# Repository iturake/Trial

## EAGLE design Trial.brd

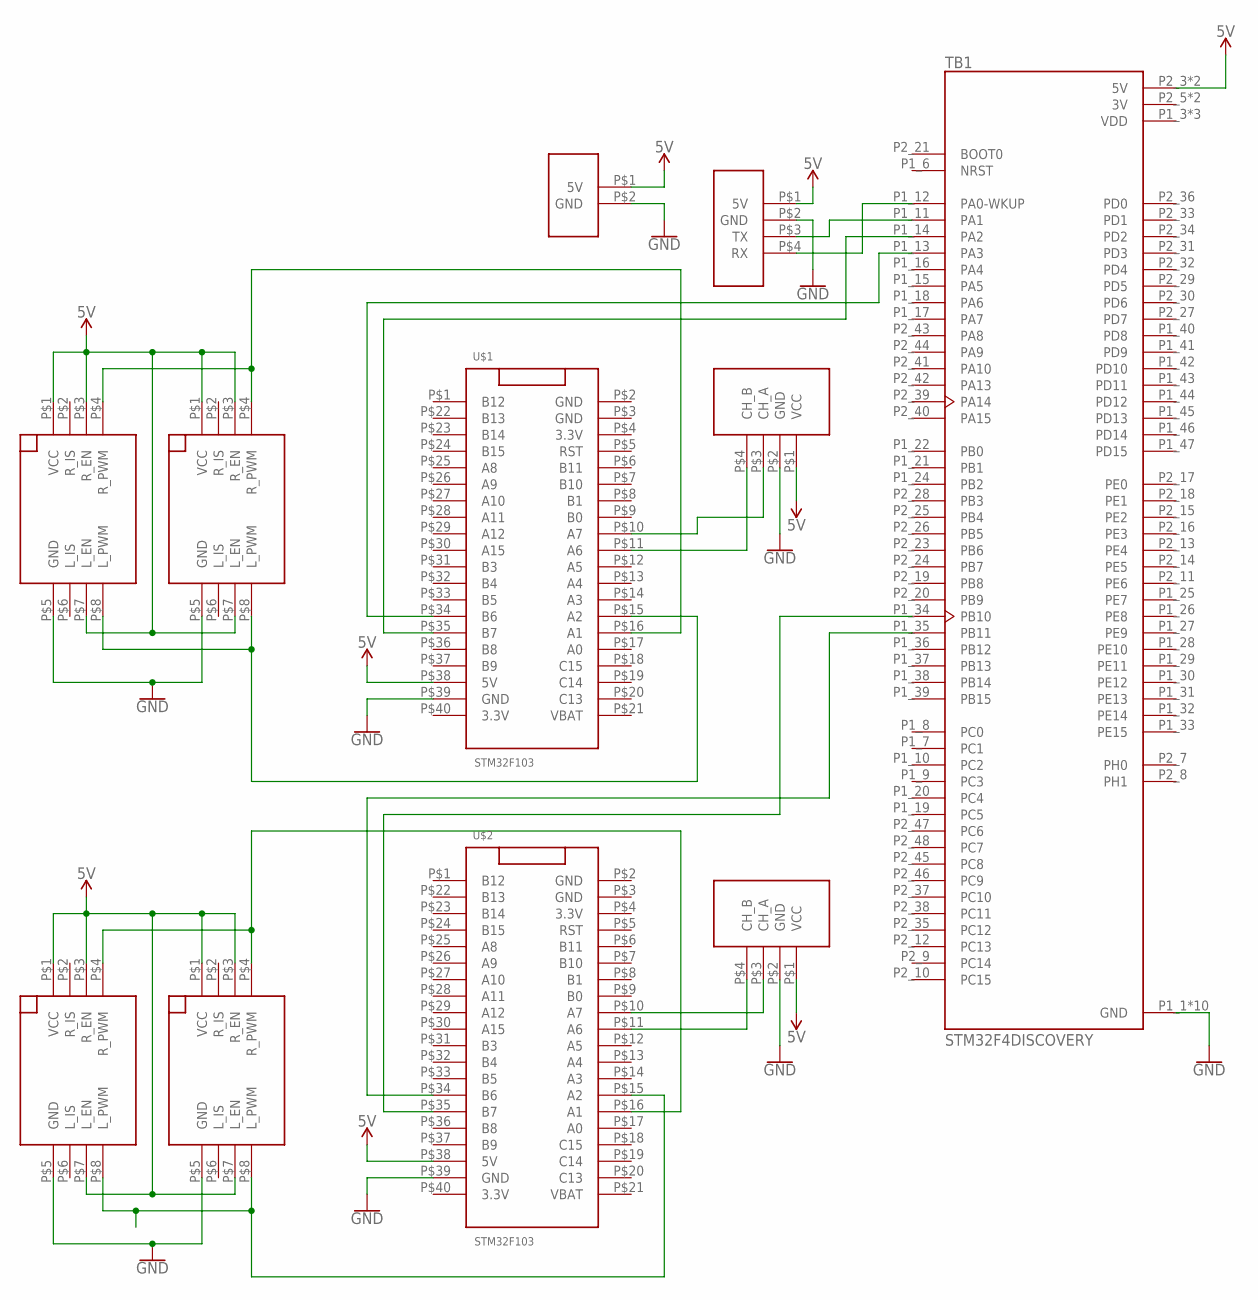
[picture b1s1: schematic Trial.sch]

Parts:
TB1: STM32F4DISCOVERY; MODULE_STM32F4DISCOVERY
U$1, U$2: STM32F103; BLUEPILL
U$3, U$4, U$5, U$6: MD_HEADER
U$7: TTL_HEADER
U$9, U$12: ENCODER_HEADER
U$11: 5V_HEADER

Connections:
3V: TB1.P2_5 (3V), TB1.P2_6 (3V)
5V: TB1.P2_3 (5V), TB1.P2_4 (5V), U$1.P$38 (5V), U$2.P$38 (5V), U$3.P$1 (VCC), U$3.P$3 (R_EN), U$3.P$7 (L_EN), U$4.P$1 (VCC), U$4.P$3 (R_EN), U$4.P$7 (L_EN), U$5.P$1 (VCC), U$5.P$3 (R_EN), U$5.P$7 (L_EN), U$6.P$1 (VCC), U$6.P$3 (R_EN), U$6.P$7 (L_EN), U$7.P$1 (5V), U$9.P$1 (VCC), U$11.P$1 (5V), U$12.P$1 (VCC)
GND: TB1.P1_1 (GND), TB1.P1_2 (GND), TB1.P1_5 (GND), TB1.P1_23 (GND), TB1.P1_49 (GND), TB1.P1_50 (GND), TB1.P2_1 (GND), TB1.P2_2 (GND), TB1.P2_49 (GND), TB1.P2_50 (GND), U$1.P$39 (GND), U$2.P$39 (GND), U$3.P$5 (GND), U$4.P$5 (GND), U$5.P$5 (GND), U$6.P$5 (GND), U$7.P$2 (GND), U$9.P$2 (GND), U$11.P$2 (GND), U$12.P$2 (GND)
unnamed: TB1.P1_12 (PA0-WKUP), U$7.P$4 (RX)
unnamed: TB1.P1_11 (PA1), U$7.P$3 (TX)
unnamed: TB1.P1_13 (PA3), U$1.P$34 (B6)
unnamed: TB1.P1_14 (PA2), U$1.P$35 (B7)
unnamed: TB1.P1_35 (PB11), U$2.P$34 (B6)
unnamed: TB1.P1_34 (PB10), U$2.P$35 (B7)
unnamed: U$1.P$15 (A2), U$5.P$8 (L_PWM), U$6.P$8 (L_PWM)
unnamed: U$1.P$11 (A6), U$9.P$4 (CH_B)
unnamed: U$1.P$10 (A7), U$9.P$3 (CH_A)
unnamed: U$2.P$11 (A6), U$12.P$4 (CH_B)
unnamed: U$2.P$10 (A7), U$12.P$3 (CH_A)
unnamed: U$1.P$16 (A1), U$5.P$4 (R_PWM), U$6.P$4 (R_PWM)
unnamed: U$2.P$15 (A2), U$3.P$8 (L_PWM), U$4.P$8 (L_PWM)
unnamed: U$2.P$16 (A1), U$3.P$4 (R_PWM), U$4.P$4 (R_PWM)
VDD: TB1.P1_3 (VDD), TB1.P1_4 (VDD), TB1.P2_22 (VDD)

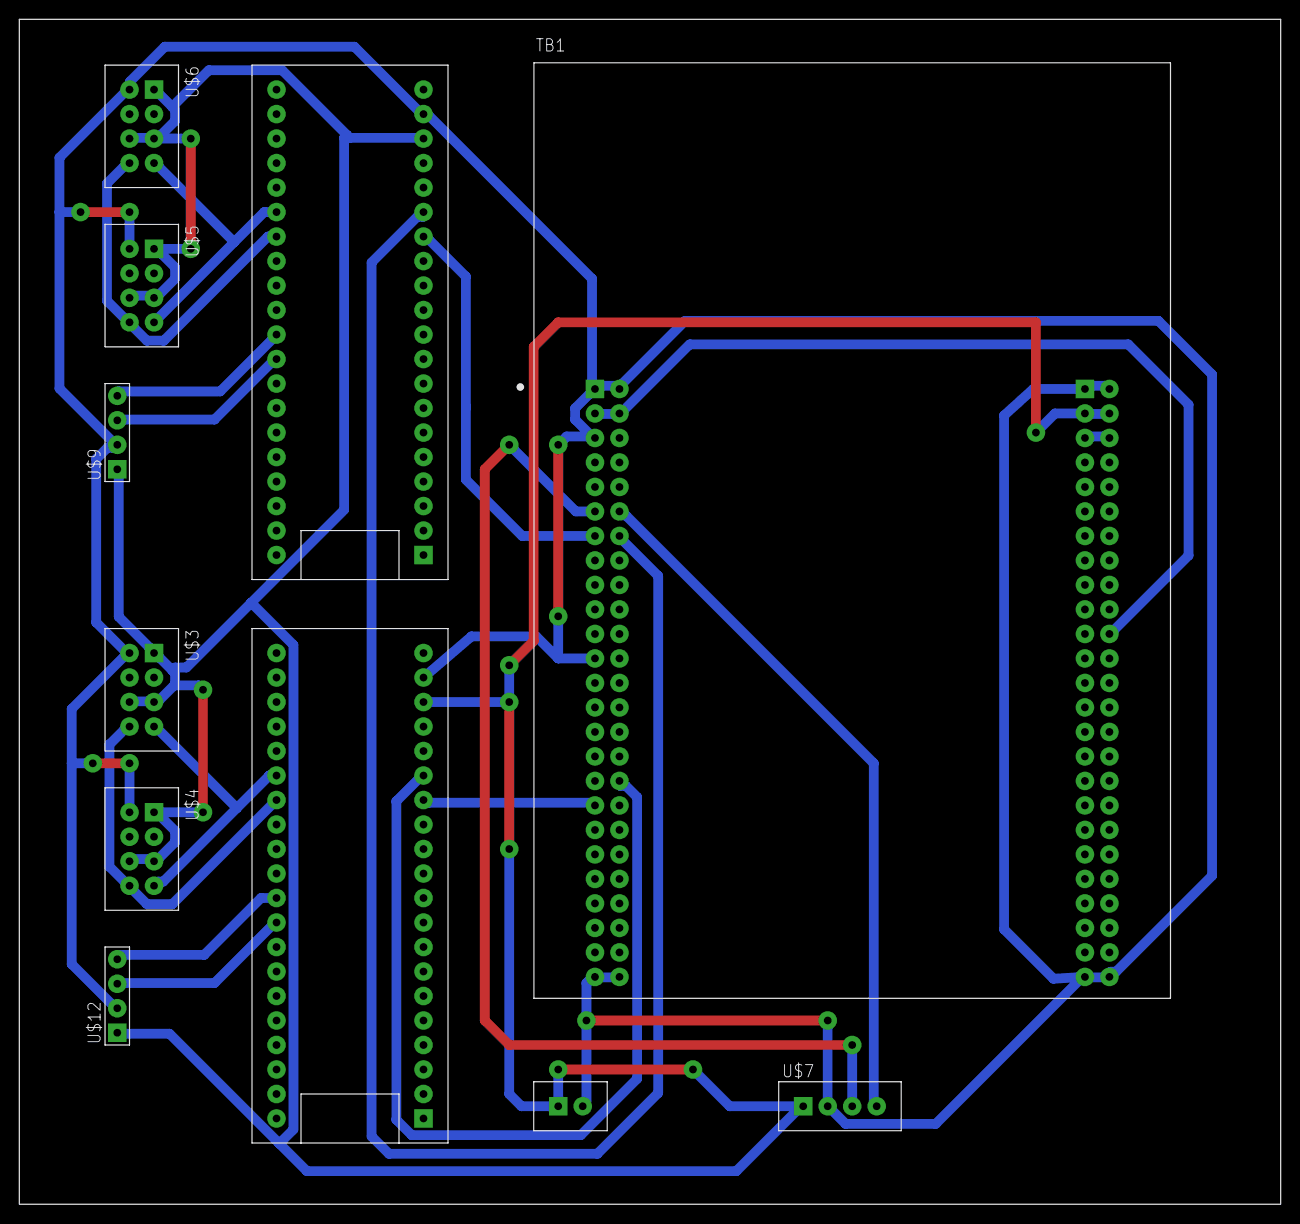
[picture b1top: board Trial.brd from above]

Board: 2 copper layers, 130.8 x 122.9 mm, 11 parts (0 on the bottom side), 18 nets.

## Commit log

2021-04-24 Edited schematic file

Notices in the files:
parts and their libraries:
SparkFun-PowerSymbols: Licensing: Creative Commons ShareAlike 4.0 International - https://creativecommons.org/licenses/by-sa/4.0
